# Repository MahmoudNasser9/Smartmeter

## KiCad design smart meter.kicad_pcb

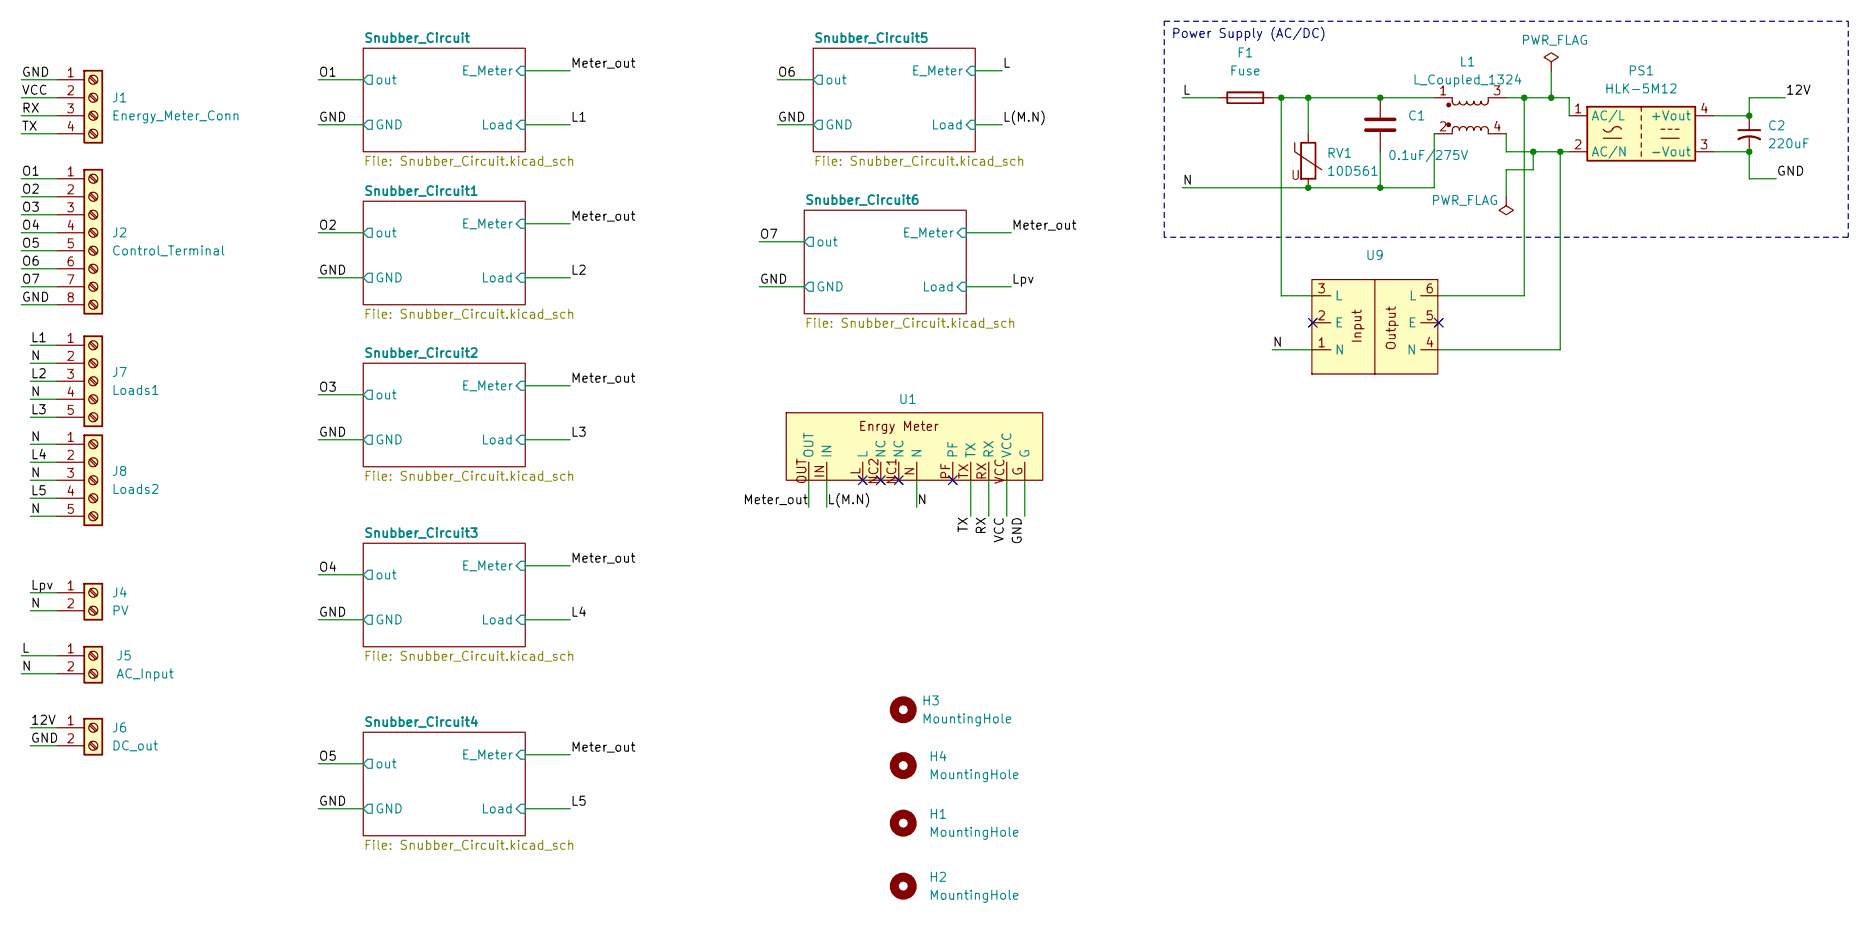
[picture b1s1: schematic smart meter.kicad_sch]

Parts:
C1: 0.1uF/275V; C_Rect_L18.0mm_W5.0mm_P15.00mm_FKS3_FKP3
C2: 220uF; C_Radial_D8.0mm_H11.5mm_P3.50mm
F1: Fuse; Fuseholder_Cylinder-5x20mm_Schurter_0031_8201_Horizontal_Op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
H1, H2, H3, H4: MountingHole; MountingHole_3mm
J1: Energy_Meter_Conn; RC4
J2: Control_Terminal; RC8
J4: PV; RPC2
J5: AC_Input; RPC2
J6: DC_out; RC2
J7: Loads1; RPC5
J8: Loads2; RPC5
L1: L_Coupled_1324; L_CommonMode_Wuerth_WE-CMB-M
PS1: HLK-5M12; Converter_ACDC_Hi-Link_HLK-5Mxx
RV1: 10D561; RV_Disc_D15.5mm_W7.5mm_P7.5mm
U1: Energy_meter
U9: AC_filter

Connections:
/12V: C2.1, J6.1, PS1.4 (+Vout)
/GND: C2.2, J1.1, J2.8, J6.2, PS1.3 (-Vout), U1.G; also elsewhere on the board
/L: F1.1, J5.1; also elsewhere on the board
/L1: J7.1; also elsewhere on the board
/L2: J7.3; also elsewhere on the board
/L3: J7.5; also elsewhere on the board
/L4: J8.2; also elsewhere on the board
/L5: J8.4; also elsewhere on the board
/L(M.N): U1.IN; also elsewhere on the board
/Lpv: J4.1; also elsewhere on the board
/Meter_out: U1.OUT; also elsewhere on the board
/N: C1.2, J4.2, J5.2, J7.2, J7.4, J8.1, J8.3, J8.5, L1.2, RV1.2, U1.N, U9.1 (N)
/O1: J2.1; also elsewhere on the board
/O2: J2.2; also elsewhere on the board
/O3: J2.3; also elsewhere on the board
/O4: J2.4; also elsewhere on the board
/O5: J2.5; also elsewhere on the board
/O6: J2.6; also elsewhere on the board
/O7: J2.7; also elsewhere on the board
/RX: J1.3, U1.RX
/TX: J1.4, U1.TX
/VCC: J1.2, U1.VCC
unnamed: C1.1, F1.2, L1.1, RV1.1, U9.3 (L)
unnamed: L1.3, PS1.1 (AC/L), U9.6 (L)
unnamed: L1.4, PS1.2 (AC/N), U9.4 (N)

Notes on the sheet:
Power Supply (AC/DC)

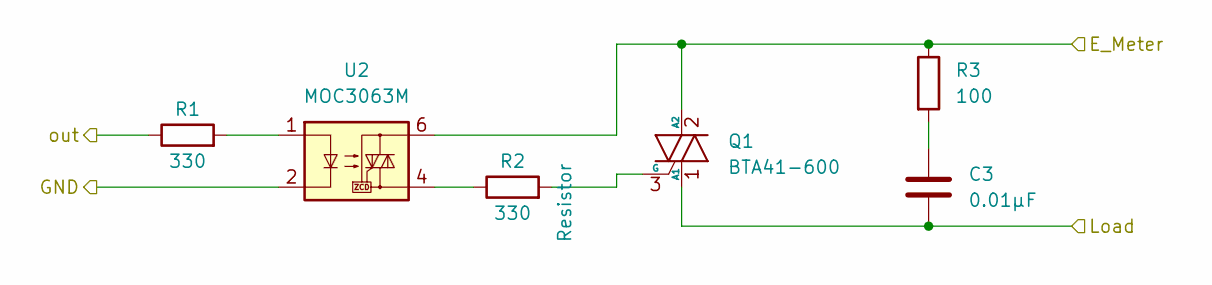
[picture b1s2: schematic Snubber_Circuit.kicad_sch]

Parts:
C3: 0.01µF; C_Rect_L13.0mm_W5.0mm_P10.00mm_FKS3_FKP3_MKS4
Q1: BTA41-600; TO-220-3_Vertical
R1, R2: 330; R_Axial_DIN0207_L6.3mm_D2.5mm_P7.62mm_Horizontal
R3: 100; R_Axial_DIN0309_L9.0mm_D3.2mm_P12.70mm_Horizontal
U2: MOC3063M; DIP-6_W7.62mm

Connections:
/GND: U2.2; also elsewhere on the board
/L1: C3.2, Q1.1 (A1); also elsewhere on the board
/Meter_out: Q1.2 (A2), R3.1, U2.6; also elsewhere on the board
/O1: R1.1; also elsewhere on the board
unnamed: C3.1, R3.2
unnamed: Q1.3 (G), R2.2
unnamed: R1.2, U2.1
unnamed: R2.1, U2.4

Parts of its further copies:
C4, C5, C6, C7, C8, C9: 0.01µF; C_Rect_L13.0mm_W5.0mm_P10.00mm_FKS3_FKP3_MKS4
Q2, Q3, Q4, Q5, Q6, Q7: BTA41-600; TO-220-3_Vertical
R4, R5, R7, R8, R10, R11, R13, R14, R16, R17, R19, R20: 330; R_Axial_DIN0207_L6.3mm_D2.5mm_P7.62mm_Horizontal
R6, R9, R12, R15, R18, R21: 100; R_Axial_DIN0309_L9.0mm_D3.2mm_P12.70mm_Horizontal
U3, U4, U5, U6, U7, U8: MOC3063M; DIP-6_W7.62mm

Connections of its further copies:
/GND: U3.2, U4.2, U5.2, U6.2, U7.2, U8.2; also elsewhere on the board
/L: Q6.2 (A2), R18.1, U7.6; also elsewhere on the board
/L2: C4.2, Q2.1 (A1); also elsewhere on the board
/L3: C5.2, Q3.1 (A1); also elsewhere on the board
/L4: C6.2, Q4.1 (A1); also elsewhere on the board
/L5: C7.2, Q5.1 (A1); also elsewhere on the board
/L(M.N): C8.2, Q6.1 (A1); also elsewhere on the board
/Lpv: C9.2, Q7.1 (A1); also elsewhere on the board
/Meter_out: Q2.2 (A2), Q3.2 (A2), Q4.2 (A2), Q5.2 (A2), Q7.2 (A2), R6.1, R9.1, R12.1, R15.1, R21.1, U3.6, U4.6, U5.6, U6.6, U8.6; also elsewhere on the board
/O2: R4.1; also elsewhere on the board
/O3: R7.1; also elsewhere on the board
/O4: R10.1; also elsewhere on the board
/O5: R13.1; also elsewhere on the board
/O6: R16.1; also elsewhere on the board
/O7: R19.1; also elsewhere on the board
unnamed: C4.1, R6.2
unnamed: C5.1, R9.2
unnamed: C6.1, R12.2
unnamed: C7.1, R15.2
unnamed: C8.1, R18.2
unnamed: C9.1, R21.2
unnamed: Q2.3 (G), R5.2
unnamed: Q3.3 (G), R8.2
unnamed: Q4.3 (G), R11.2
unnamed: Q5.3 (G), R14.2
unnamed: Q6.3 (G), R17.2
unnamed: Q7.3 (G), R20.2
unnamed: R4.2, U3.1
unnamed: R5.1, U3.4
unnamed: R7.2, U4.1
unnamed: R8.1, U4.4
unnamed: R10.2, U5.1
unnamed: R11.1, U5.4
unnamed: R13.2, U6.1
unnamed: R14.1, U6.4
unnamed: R16.2, U7.1
unnamed: R17.1, U7.4
unnamed: R19.2, U8.1
unnamed: R20.1, U8.4

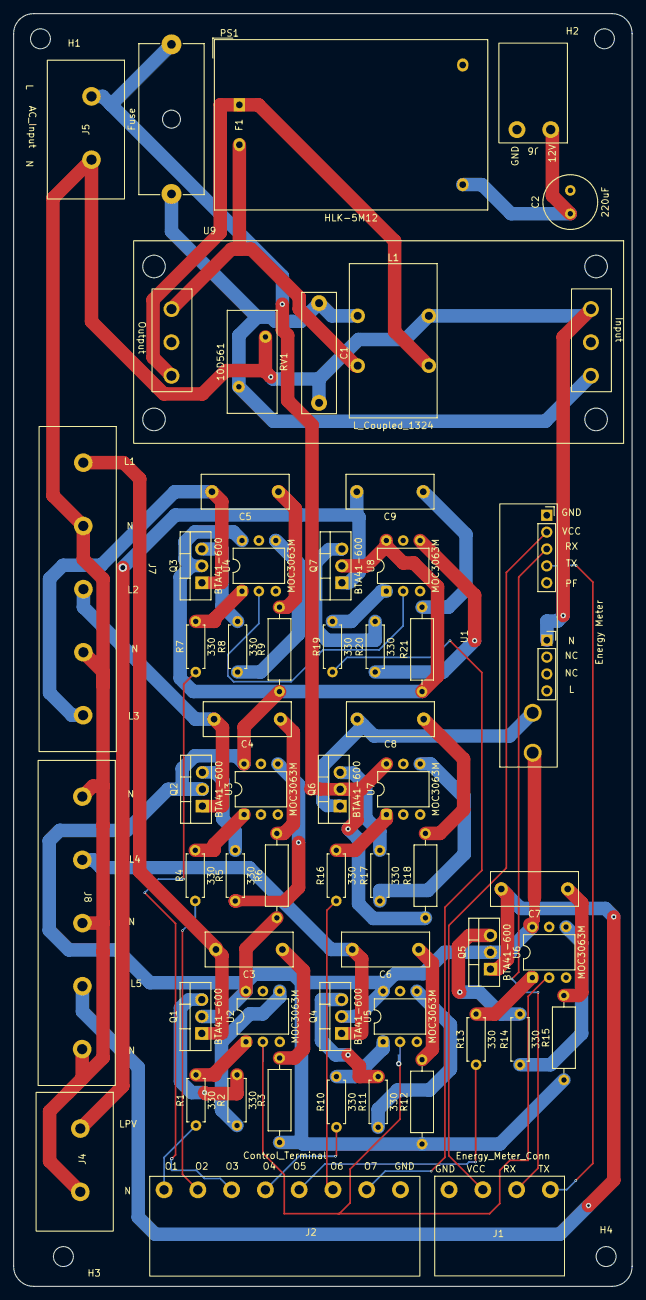
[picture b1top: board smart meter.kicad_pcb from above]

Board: 2 copper layers, 93.0 x 191.5 mm, 61 parts (0 on the bottom side), 53 nets.

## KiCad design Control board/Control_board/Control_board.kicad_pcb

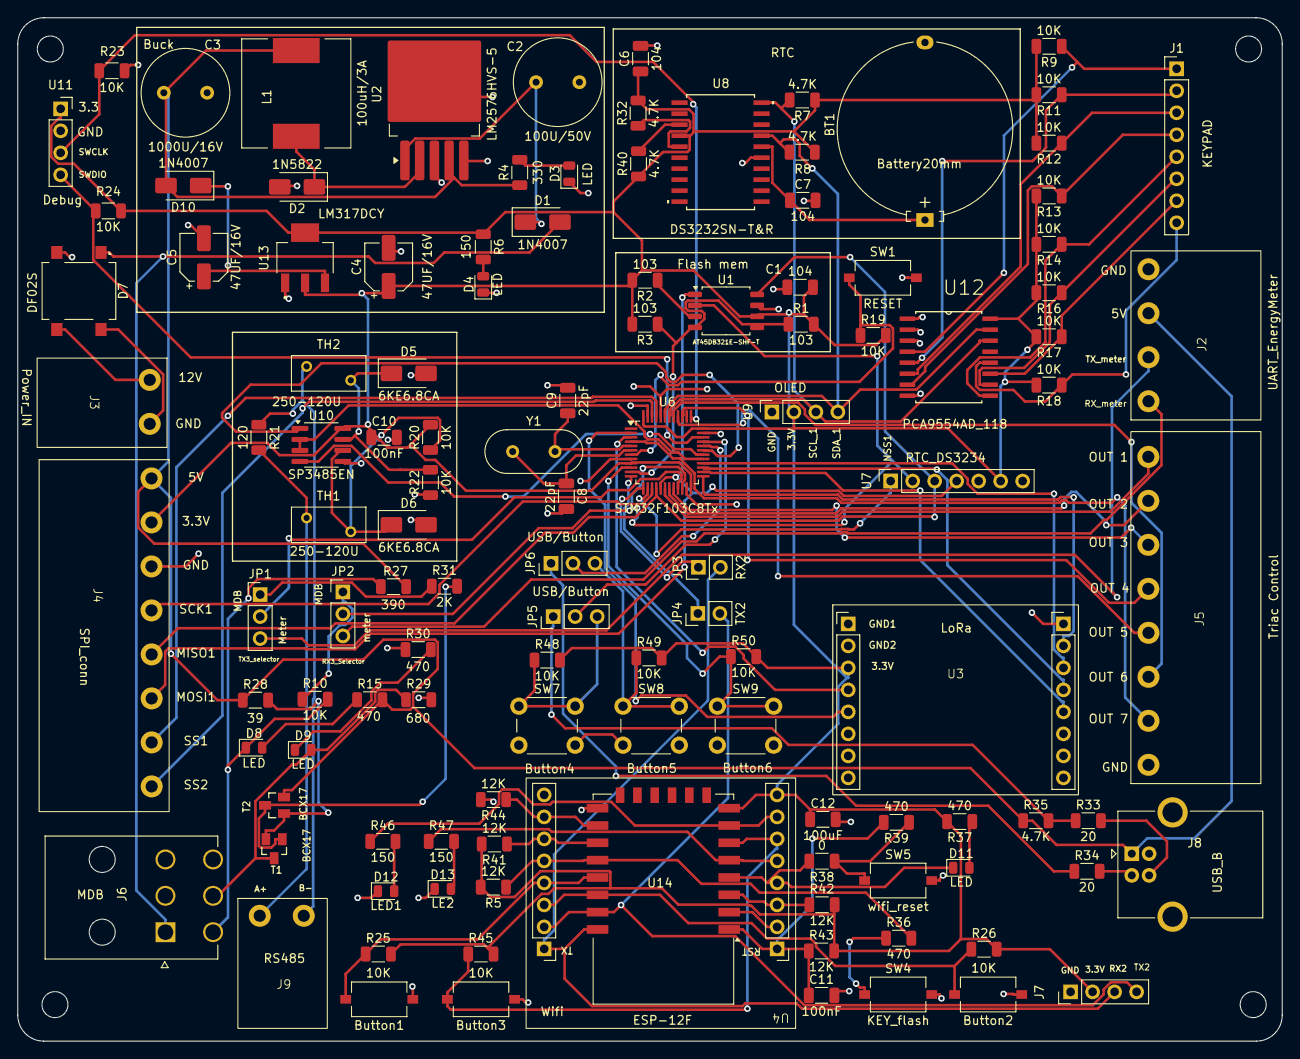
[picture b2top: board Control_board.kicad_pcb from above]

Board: 2 copper layers, 146.0 x 118.2 mm, 123 parts (0 on the bottom side), 99 nets.

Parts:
BT1: Battery20mm; Battery_Panasonic_CR2032-HFN_Horizontal_CircularHoles
C1, C6, C7: 104; C_1206_3216Metric
C2: 100U/50V; C_Radial_D10.0mm_H12.5mm_P5.00mm
C3: 1000U/16V; C_Radial_D10.0mm_H12.5mm_P5.00mm
C4, C5: 47UF/16V; CP_Elec_5x5.3
C8, C9: 22pF; C_1206_3216Metric
C10, C11: 100nF; C_1206_3216Metric
C12: 100uF; C_1206_3216Metric
D1, D10: 1N4007; D_SMA
D2: 1N5822; D_SMA
D3, D4, D8, D9, D11: LED; LED_0805_2012Metric
D5, D6: 6KE6.8CA; D_SMA
D7: DF02S; Diode_Bridge_OnSemi_SDIP-4L
D12: LED1; LED_0805_2012Metric
D13: LE2; LED_0805_2012Metric
H1, H2, H3, H4: MountingHole; MountingHole_3mm
J1: KEYPAD; PinHeader_1x08_P2.54mm_Vertical
J2: UART_EnergyMeter; RC4
J3: Power_IN; RC2
J4: SPI_conn; RC8
J5: Triac Control; RC8
J6: MDB
J7: UART_wifi; PinHeader_1x04_P2.54mm_Vertical
J8: USB_B; USB_B_OST_USB-B1HSxx_Horizontal
J9: RS485; RC2
JP1: TX3_selector; PinHeader_1x03_P2.54mm_Vertical
JP2: RX3_Selector; PinHeader_1x03_P2.54mm_Vertical
JP3: RX2; PinHeader_1x02_P2.54mm_Vertical
JP4: TX2; PinHeader_1x02_P2.54mm_Vertical
JP5, JP6: USB/Button; PinHeader_1x03_P2.54mm_Vertical
L1: 100uH/3A; L_12x12mm_H8mm
R1, R2, R3: 103; R_1206_3216Metric
R4: 330; R_1206_3216Metric
R5, R41, R42, R43, R44: 12K; R_1206_3216Metric
R6, R46, R47: 150; R_1206_3216Metric
R7, R8, R32, R35, R40: 4.7K; R_1206_3216Metric
R9, R10, R11, R12, R13, R14, R16, R17, R18, R19, R20, R22, R23, R24, R25, R26, R45, R48, R49, R50: 10K; R_1206_3216Metric
R15, R30, R36, R37, R39: 470; R_1206_3216Metric
R21: 120; R_1206_3216Metric
R27: 390; R_1206_3216Metric
R28: 39; R_1206_3216Metric
R29: 680; R_1206_3216Metric
R31: 2K; R_1206_3216Metric
R33, R34: 20; R_1206_3216Metric
R38: 0; R_1206_3216Metric
SW1: RESET; SW_Tactile_SPST_NO_Straight_CK_PTS636Sx25SMTRLFS
SW2: Button1; SW_Tactile_SPST_NO_Straight_CK_PTS636Sx25SMTRLFS
SW3: Button2; SW_Tactile_SPST_NO_Straight_CK_PTS636Sx25SMTRLFS
SW4: KEY_flash; SW_Tactile_SPST_NO_Straight_CK_PTS636Sx25SMTRLFS
SW5: wifi_reset; SW_Tactile_SPST_NO_Straight_CK_PTS636Sx25SMTRLFS
SW6: Button3; SW_Tactile_SPST_NO_Straight_CK_PTS636Sx25SMTRLFS
SW7: Button4; SW_PUSH_6mm
SW8: Button5; SW_PUSH_6mm
SW9: Button6; SW_PUSH_6mm
T1, T2: BCX17
TH1, TH2: 250-120U; Fuse_BelFuse_0ZRE0005FF_L8.3mm_W3.8mm
U1: AT45DB321E-SHF-T; SOIC-8_5.3x5.3mm_P1.27mm
U2: LM2576HVS-5; TO-263-5_TabPin3
U3: LoRa
U4: Wifi; wifi
U6: STM32F103C8Tx; LQFP-48_7x7mm_P0.5mm
U7: RTC_DS3234; PinSocket_1x07_P2.54mm_Vertical
U8: DS3232SN-T&R; RTC_3232
U9: OLED; PinSocket_1x04_P2.54mm_Vertical
U10: SP3485EN; SOIC-8_3.9x4.9mm_P1.27mm
U11: Debug; PinSocket_1x04_P2.54mm_Vertical
U12: PCA9554AD_118; PCA955
U13: LM317DCY; LM3.3V
U14: ESP-12F; ESP-12E
Y1: 8MHZ; Crystal_HC18-U_Vertical

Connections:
/3.3V: C1.1, C4.1, C6.1, C10.1, C12.1, J4.2, J7.2, R1.2, R2.2, R3.2, R5.2, R6.1, R7.1, R8.1, R9.2, R11.2, R12.2, R13.2, R14.2, R16.2, R17.2, R18.2, R19.2, R20.2, R24.2, R25.2, R26.2, R32.2, R37.2, R40.1, R41.2, R42.2, R43.2, R45.2, R48.2, R49.2, R50.2, U1.6 (VCC), U3.3.3V, U4.VCC, U6.9 (VDDA), U6.24 (VDD), U6.36 (VDD), U6.48 (VDD), U7.6, U8.4 (VCC), U9.2, U10.8 (VCC), U11.1, U12.16 (VDD), U13.2 (OUTPUT), U13.4 (OUTPUT), U14.8 (VCC)
/5V: C3.1, D10.2 (A), J2.3, J4.1, J8.1 (VBUS), L1.2, R4.1, R15.2, R27.2, R28.1, R35.1, T2.2, U2.4 (FB)
/12V: D1.2 (A), D7.1 (+), J6.1
/A+: J9.1, R21.2, TH1.1
/ADC: U4.ADC, U14.2 (ADC)
/B-: J9.2, R21.1, TH2.1
/Button1: R25.1, SW2.1, U4.GPIO4, U14.19 (GPIO4)
/Button2: R26.1, SW3.1, U4.GPIO5, U14.20 (GPIO5)
/Button3: R45.1, SW6.1, U4.GPIO12, U14.6 (GPIO12)
/Button4: JP5.3 (B), R48.1, SW7.1
/Button5: JP6.3 (B), R49.1, SW8.1
/Button6: R50.1, SW9.1, U6.10 (PA0)
/CS_flash: R1.1, R3.1, U1.4 (~CS), U1.5 (~WP), U6.11 (PA1)
/DIO0: U3.DIO0, U6.2 (PC13)
/EN: R42.1, U4.CH_PC, U14.3 (EN)
/GND: BT1.2 (-), C1.2, C2.2, C3.2, C4.2, C5.2, C6.2, C7.2, C8.2, C9.2, C10.2, C11.2, C12.2, D2.2 (A), D3.1 (K), D4.1 (K), D5.2 (A), D6.2 (A), D7.2 (-), D12.1 (K), D13.1 (K), J2.4, J4.3, J5.1, J6.2, J6.6, J7.1, J8.4 (GND), J8.5 (Shield), R22.1, R23.2, R29.2, R30.1, R44.2, SW1.2, SW2.2, SW3.2, SW4.2, SW5.2, SW6.2, SW7.2, SW8.2, SW9.2, U1.7 (GND), U2.3 (GND), U2.5 (~ON/OFF), U3.GND1 (GND), U3.GND2 (GND), U3.GND3 (GND), U3.GND4 (GND), U4.GND, U6.8 (VSSA), U6.23 (VSS), U6.35 (VSS), U6.44 (BOOT0), U6.47 (VSS), U7.7, U8.15 (GND), U9.1, U10.5 (GND), U11.2, U12.1 (A0), U12.2 (A1), U12.3 (A2), U12.8 (VSS), U13.1 (ADJUST), U14.15 (GND)
/GPIO0: R5.1, R36.2, U4.GPIO0, U14.18 (GPIO0)
/GPIO2: R41.1, U4.GPIO2, U14.17 (GPIO2)
/GPIO15: R44.1, U4.GPIO15, U14.16 (GPIO15)
/GPIO16: D11.1 (K), R38.2, U4.GPIO16, U14.4 (GPIO16)
/GPIO_1: J4.7, U6.45 (PB8)
/GPIO_2: J4.8, U6.46 (PB9)
/KEY1: J1.1, R9.1, U12.4 (IO0)
/KEY2: J1.2, R11.1, U12.5 (IO1)
/KEY3: J1.3, R12.1, U12.6 (IO2)
/KEY4: J1.4, R13.1, U12.7 (IO3)
/KEY5: J1.5, R14.1, U12.9 (IO4)
/KEY6: J1.6, R16.1, U12.10 (IO5)
/KEY7: J1.7, R17.1, U12.11 (IO6)
/KEY8: J1.8, R18.1, U12.12 (IO7)
/LED 1: R46.1, U4.GPIO13, U14.7 (GPIO13)
/LED 2: R47.1, U4.GPIO14, U14.5 (GPIO14)
/MDB_uart/MR: D8.1 (K), J6.4, R10.2, R27.1
/MDB_uart/MT: D9.2 (A), J6.5, R29.1, T1.3
/MISO1: J4.5, U1.8 (SO), U6.16 (PA6), U7.3
/MISO2: U3.MISO, U6.27 (PB14)
/MOSI1: J4.6, U1.1 (SI), U6.17 (PA7), U7.4
/MOSI2: U3.MOSI, U6.28 (PB15)
/NRST: R19.1, SW1.1, U6.7 (NRST)
/NSS1: U6.14 (PA4), U7.1
/NSS2: U3.NSS, U6.25 (PB12)
/OSC_IN: C9.1, U6.5 (PD0), Y1.2
/OSC_OUT: C8.1, U6.6 (PD1), Y1.1
/OUT1: J5.8, U6.18 (PB0)
/OUT2: J5.7, U6.19 (PB1)
/OUT3: J5.6, U6.20 (PB2)
/OUT4: J5.5, U6.39 (PB3)
/OUT5: J5.4, U6.40 (PB4)
/OUT6: J5.3, U6.41 (PB5)
/OUT7: J5.2, U6.4 (PC15)
/PA11: JP6.2 (C), U6.32 (PA11)
/PA12: JP5.2 (C), U6.33 (PA12)
/RST_LoRa: U3.RST, U6.3 (PC14)
/RST_WIFI: C11.1, R39.2, R43.1, U4.REST, U14.1 (~RST)
/RX1: U6.31 (PA10), U10.1 (RO)
/RX2: J7.3, JP3.2 (B), U4.TX, U14.22 (GPIO1/TXD)
/RX2_stm: JP3.1 (A), U6.13 (PA3)
/RX3: JP2.2 (C), U6.22 (PB11)
/RX_MDB: JP2.1 (A), R10.1
/RX_Meter: J2.1, JP2.3 (B)
/SCK1: J4.4, U1.2 (SCK), U6.15 (PA5), U7.2
/SCK2: U3.SCK, U6.26 (PB13)
/SCL_1: R7.2, U6.42 (PB6), U8.20 (SCL), U9.3, U12.14 (SCL)
/SDA_1: R8.2, U6.43 (PB7), U8.17 (SDA), U9.4, U12.15 (SDA)
/SWCLK: R23.1, U6.37 (PA14), U11.3
/SWDIO: R24.1, U6.34 (PA13), U11.4
/TX1: U6.30 (PA9), U10.4 (DI)
/TX2: J7.4, JP4.2 (B), U4.RX, U14.21 (GPIO3/RXD)
/TX2_stm: JP4.1 (A), U6.12 (PA2)
/TX3: JP1.2 (C), U6.21 (PB10)
/TX_EN: U6.29 (PA8), U10.2 (~RE), U10.3 (DE)
/TX_MDB: JP1.1 (A), R31.1
/TX_Meter: J2.2, JP1.3 (B)
/USB_DM: JP6.1 (A), R34.1
/USB_DP: JP5.1 (A), R33.1, R35.2
unnamed: BT1.1 (+), C7.1, U8.16 (VBAT)
unnamed: C2.1, D1.1 (K), U2.1 (VIN)
unnamed: D2.1 (K), L1.1, U2.2 (OUT)
unnamed: D3.2 (A), R4.2
unnamed: D4.2 (A), R6.2
unnamed: D5.1 (K), R22.2, TH2.2, U10.7 (B)
unnamed: D6.1 (K), R20.1, TH1.2, U10.6 (A)
unnamed: D8.2 (A), R15.1
unnamed: D9.1 (K), R30.2
unnamed: C5.1, D10.1 (K), U13.3 (INPUT)
unnamed: D11.2 (A), R37.1
unnamed: D12.2 (A), R46.2
unnamed: D13.2 (A), R47.2
unnamed: D7.3, J3.1
unnamed: D7.4, J3.2
unnamed: J8.3 (D+), R33.2
unnamed: J8.2 (D-), R34.2
unnamed: R28.2, T1.2, T2.1
unnamed: R31.2, T1.1, T2.3
unnamed: R36.1, SW4.1
unnamed: R38.1, R39.1, SW5.1
unnamed: R2.1, U1.3 (~RESET)
unnamed: R40.2, U8.3 (32KHZ)
unnamed: R32.1, U8.5 (*INT/SQW)

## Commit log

2025-06-02 Add project files
2025-06-04 edit layout
2025-07-28 Add ic to external GPIO
2025-08-23 Routing Power ctr
2025-08-23 Routing control board
2025-08-24 last edit
2025-08-26 last update
